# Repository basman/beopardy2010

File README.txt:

Jeopardy game setup with software, hardware and firmware
based on the CCC beopardy project (2010).

Instead of the original CCC's microcontroller, this project uses an
Arduino Nano to control the buttons and lamps. The serial protocol
has been extended to indicate exactly at all times during the game
which players may buzz in and when.

The repo contains the following subdirectories:

arduino         - the firmware for the Arduino Nano, controlling the
                  button lamps and signalling the buttons over the 
                  serial port to the PC/laptop running beopardy_2010

beopardy_2010   - the Jeopardy game software, written in Perl+Tk
                  This program displays the game board and implements
                  the game.

hardware        - the game controller for push buttons and their lamps

References:

The code this fork is based on:
http://blogmal.42.org/misc/beopardy-2010.story

The legacy code with the different versions used at the CCC throughout the
years:
https://github.com/Sec42/beopardy-legacy

The new web based beopardy by Sec:
https://github.com/Sec42/beopardy

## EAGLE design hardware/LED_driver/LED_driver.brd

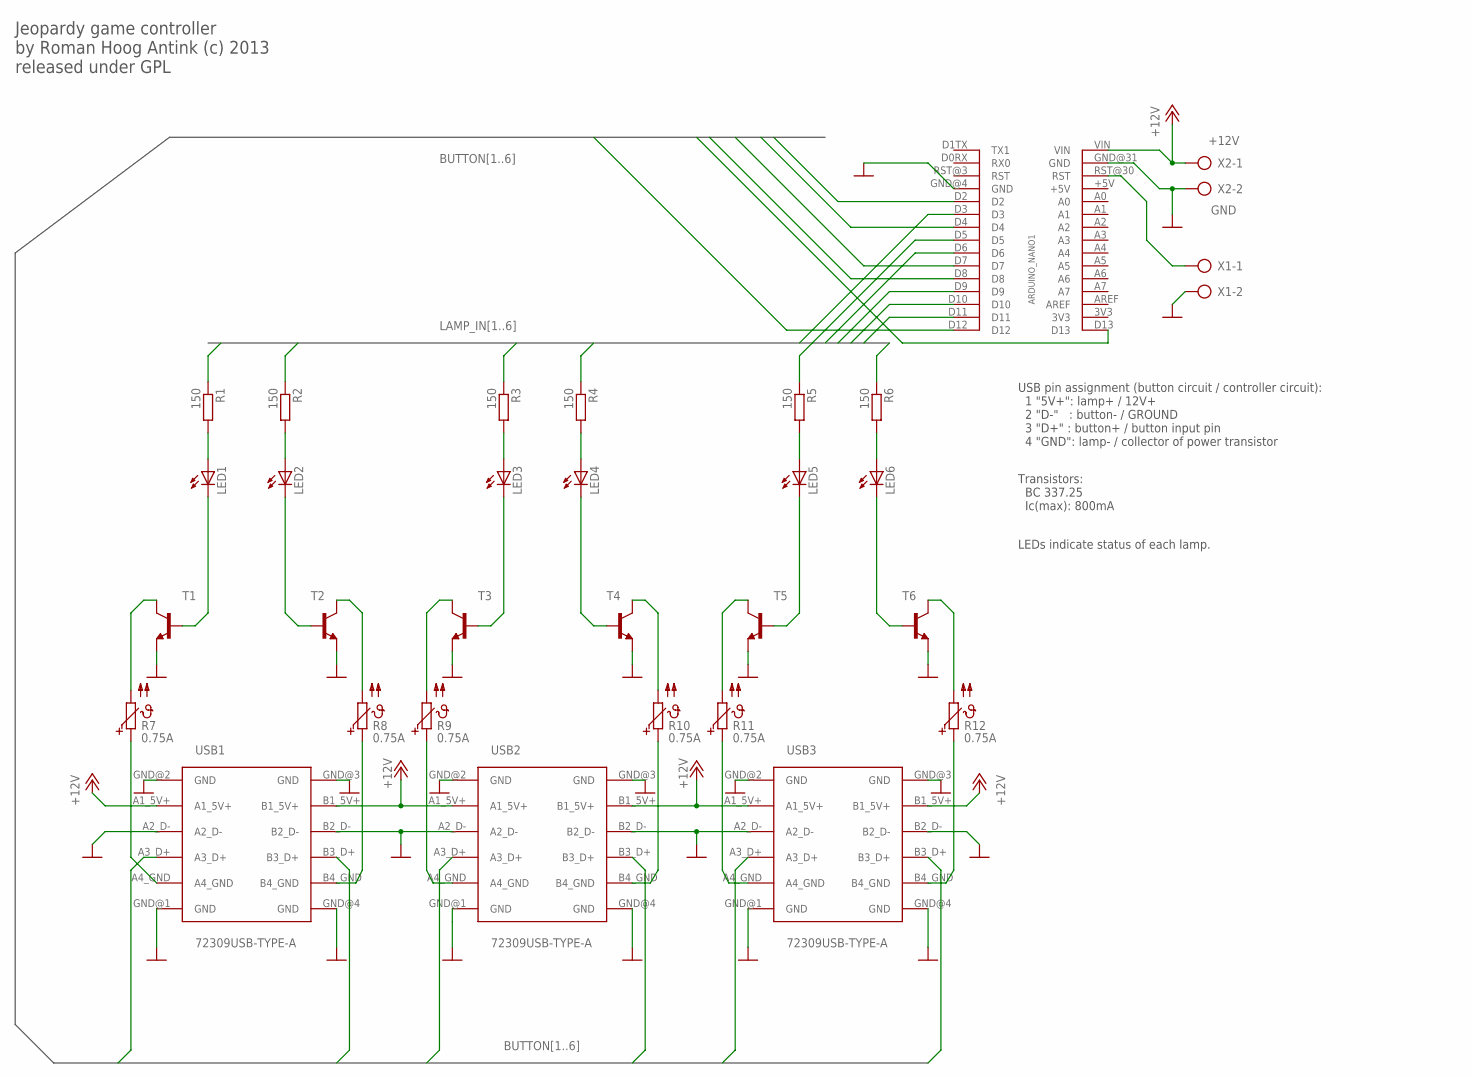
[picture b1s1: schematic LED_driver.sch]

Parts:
ARDUINO_NANO1: ARDUINO-NANO-SHIELD-CON
LED1, LED2, LED3, LED4, LED5, LED6: LED3MM
R1, R2, R3, R4, R5, R6: 150; 0207/10
R7, R8, R9, R10, R11, R12: 0.75A; PTC
T1, T2, T3, T4, T5, T6: -NPN-TO92; TO92
USB1, USB2, USB3: 72309USB-TYPE-A; 72309
X1, X2: AK300/2

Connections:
+12V: ARDUINO_NANO1.VIN, USB1.A1_5V+, USB1.B1_5V+, USB2.A1_5V+, USB2.B1_5V+, USB3.A1_5V+, USB3.B1_5V+, X2.1
BUTTON1: ARDUINO_NANO1.D2, USB1.A3_D+
BUTTON2: ARDUINO_NANO1.D4, USB1.B3_D+
BUTTON3: ARDUINO_NANO1.D7, USB2.A3_D+
BUTTON4: ARDUINO_NANO1.D8, USB2.B3_D+
BUTTON5: ARDUINO_NANO1.D12, USB3.A3_D+
BUTTON6: ARDUINO_NANO1.D13, USB3.B3_D+
GND: ARDUINO_NANO1.GND@4 (GND), ARDUINO_NANO1.GND@31 (GND), T1.1 (E), T2.1 (E), T3.1 (E), T4.1 (E), T5.1 (E), T6.1 (E), USB1.A2_D-, USB1.B2_D-, USB1.GND@1 (GND), USB1.GND@2 (GND), USB1.GND@3 (GND), USB1.GND@4 (GND), USB2.A2_D-, USB2.B2_D-, USB2.GND@1 (GND), USB2.GND@2 (GND), USB2.GND@3 (GND), USB2.GND@4 (GND), USB3.A2_D-, USB3.B2_D-, USB3.GND@1 (GND), USB3.GND@2 (GND), USB3.GND@3 (GND), USB3.GND@4 (GND), X1.2, X2.2
LAMP_IN1: ARDUINO_NANO1.D3, R1.1
LAMP_IN2: ARDUINO_NANO1.D5, R2.1
LAMP_IN3: ARDUINO_NANO1.D6, R3.1
LAMP_IN4: ARDUINO_NANO1.D9, R4.1
LAMP_IN5: ARDUINO_NANO1.D10, R5.1
LAMP_IN6: ARDUINO_NANO1.D11, R6.1
unnamed: LED6.A, R6.2
unnamed: R7.2, T1.3 (C)
unnamed: R8.1, USB1.B4_GND
unnamed: R9.1, USB2.A4_GND
unnamed: R10.2, T4.3 (C)
unnamed: R11.1, USB3.A4_GND
unnamed: LED1.K (C), T1.2 (B)
unnamed: LED2.K (C), T2.2 (B)
unnamed: LED3.K (C), T3.2 (B)
unnamed: LED4.K (C), T4.2 (B)
unnamed: LED5.K (C), T5.2 (B)
unnamed: LED6.K (C), T6.2 (B)
unnamed: R12.2, T6.3 (C)
unnamed: LED5.A, R5.2
unnamed: LED4.A, R4.2
unnamed: LED3.A, R3.2
unnamed: LED2.A, R2.2
unnamed: LED1.A, R1.2
unnamed: ARDUINO_NANO1.RST@30 (RST), X1.1
unnamed: R7.1, USB1.A4_GND
unnamed: R8.2, T2.3 (C)
unnamed: R9.2, T3.3 (C)
unnamed: R10.1, USB2.B4_GND
unnamed: R11.2, T5.3 (C)
unnamed: R12.1, USB3.B4_GND

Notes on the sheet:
USB pin assignment (button circuit / controller circuit): 1 "5V+": lamp+ / 12V+ 2 "D-" : button- / GROUND 3 "D+" : button+ / button input pin 4 "GND": lamp- / collector of power transistor
Jeopardy game controller by Roman Hoog Antink (c) 2013 released under GPL
Transistors: BC 337.25 Ic(max): 800mA
LEDs indicate status of each lamp.

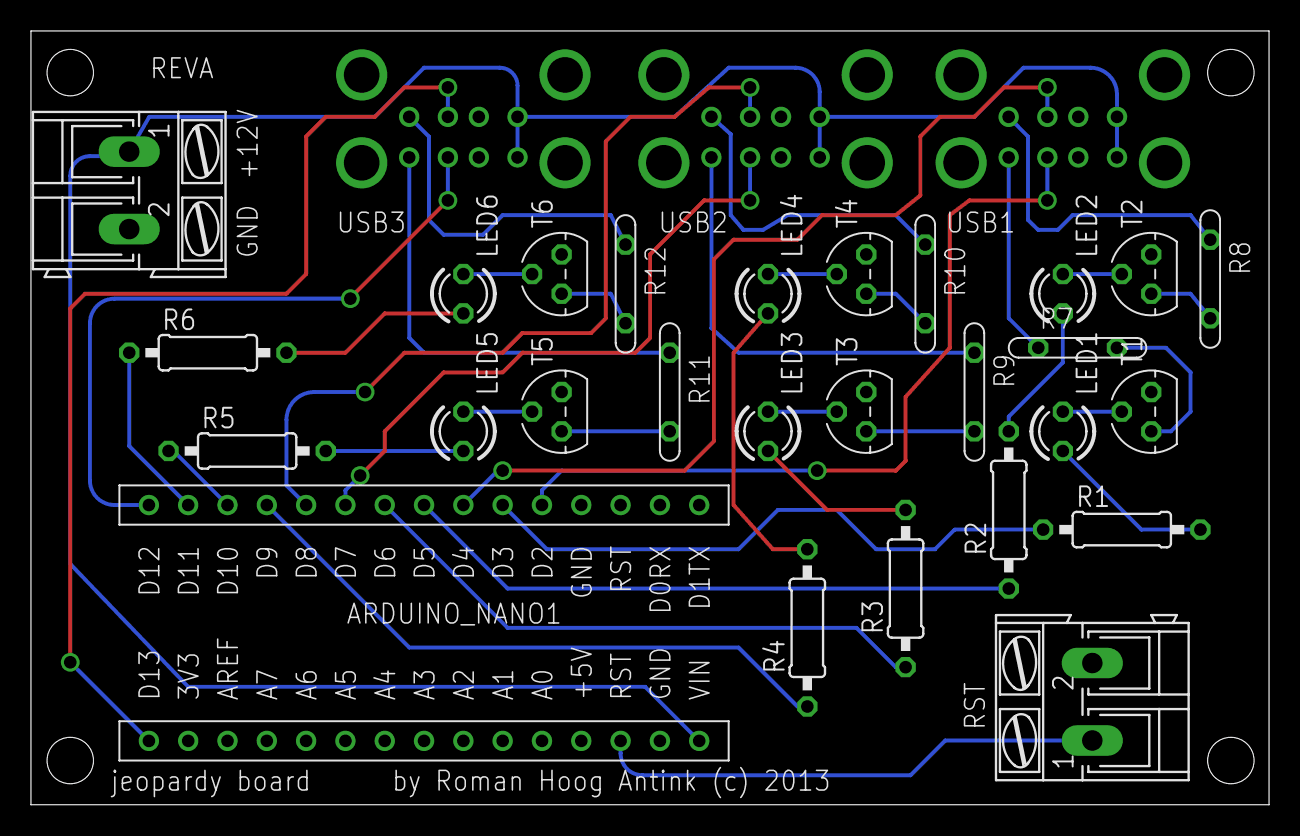
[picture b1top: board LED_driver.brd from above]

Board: 2 copper layers, 80.0 x 50.0 mm, 30 parts (0 on the bottom side), 39 nets.

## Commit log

2013-03-29 initial import (implementation of original CCC protocol)
2013-04-02 adjust all pins. add minimum lamp control.
2013-04-03 new feature: suppress buttons
2013-04-12 animate lamps and fix button suppression
2013-04-14 ignore carriage return
2013-04-14 code cleanup: remove trailing spaces
2013-04-14 import CCC beopardy 2010
2013-04-14 set serial /dev/ttyUSB0, speed 9600
2013-04-14 soundd: disable mood
2013-04-14 beopardy: add file access error messages
2013-04-14 beopardy: edit font selectors for Ubuntu 12.04
2013-04-14 add dummy input files, so beopardy can start
2013-04-20 configure for 6 players
2013-04-22 implement O command: oops, ignore last button
2013-04-22 add serial protocol documentation
2013-04-22 add error response to serial documentation
2013-04-23 cleanup TODO
2013-04-23 fix comment
2013-04-23 reset lamps after F (false) and O (oops) commands
2013-05-04 lamp animation: quick first flash
2013-05-09 begin implementation of serial protocol extension
2013-05-09 implement command 'N', switching off all buttons and lamps
2013-05-09 improve error message (connect sound server)
2013-05-09 more of serial protocol extension
2013-05-09 use serial command 'N' to silence all buttons and lamps after 'Start' has been clicked
2013-05-09 don't reset board if empty string received from board
2013-07-21 disable "Hey, ray!" popup
2013-07-21 fix unitialized warning
2013-07-22 try multiple ttyUSBx ports
2013-07-22 show popup when serial connection is lost
2013-07-22 create TODO
2013-07-22 open serial port without creating file and no clobber
2013-07-22 ser_reset may be used as callback or called directly
2013-07-22 suppress warning about non numerical serial input
2013-07-22 improve serial input message
2013-07-22 fix ser_reset argument semantics
2013-07-22 fix failing ser_reset during startup
2013-07-22 add .gitignore
2013-07-22 again fix failing ser_reset at startup
2013-07-23 rephrase serial protocol documentation
2013-07-23 add hardware design (eagle and gerber files)
2013-07-23 add README.txt
2013-07-23 extend README.txt
2013-07-23 TODO: ser_reset during startup not solved
2013-07-23 add RTFM.ubuntu
2013-07-23 mark TODO
2013-07-23 move arduino files into subdirectory
    The arduino IDE complains otherwize when opening the source code
    beopardy.ino
2013-07-23 replace lamp animation algorithm
    The old algorithm was static. The new algo is based on parametrisation.
2013-07-26 comments and cosmetics
2013-07-26 reset buttons upon question begin
2013-07-26 wait for arduino to initialize
2013-07-26 Revert "fix failing ser_reset during startup"
    ser_reset is no longer used as first communication to game controller,
    so the retry thing has been removed.
2013-07-26 fix ser_startup()
2013-07-26 improve handling of serial disruption
2013-07-26 default to 4 players
2013-07-26 TODO: button activation delay and penalty
2013-07-26 reduce hardware startup delay
2013-08-24 update TODO
2013-09-03 soundd: add .aac file type
2013-09-03 beopardy: avoid reset 'F' if no button pressed
2013-09-03 beopardy: support JPG and PNG images
2013-09-03 beopardy: use UTF-8 encoding for input files
2013-09-03 beopardy: introduce new font size for categories
2013-09-03 beopardy: update error message and comments
2013-09-03 beopardy: no button reset on double jeopardy
2013-09-03 beopardy: use pixmap image in Jeopardy
2013-09-03 arduino: new command 1,2,3,...
2013-09-03 beopardy: convert source code to UTF-8
2013-09-03 beopardy: fix double jeopardy serial communication
2013-09-03 soundd: use mplayer for mp3
2013-09-03 beopardy: leave button locked after correct answer
2013-09-03 beopardy: fix indentation
2013-10-05 autostart of soundd
2013-10-05 begin implementation of hwproxy
2013-10-09 hwproxy: continue implementation
2013-10-09 arduino: fix R,N,1,F suppressing all buttons (double jeopardy)
2013-10-09 new question directory structure (reorganise sample files)
2013-10-09 implement new question directory structure
2013-10-09 fix regression of double jeopardy by new question directory structure
2013-10-09 update docu (new question directory structure)
2013-10-10 hwproxy: add MAC usbserial file pattern
2013-10-10 hwproxy: comment explaining mapping and grouping
2013-10-10 hwproxy: implement data relay
2013-10-10 hwproxy: implement hardware state recovery
2013-10-10 hwproxy: IO tweaking
2013-10-10 add 6th player's color
2013-10-10 update Test.jg to load without error (new question directory structure)
2013-10-10 hwproxy: fix hardware state recovery
2013-10-10 beopardy: no splash screen with readfile (-r)
2013-10-10 hwproxy: fix autostart of soundd and hwproxy
2013-10-11 hwproxy: cleanup message
2013-10-11 hwproxy: implement hardware emulator (-e)
2013-10-11 beopardy: improve hardware disconnect robustness
2013-10-11 beopardy: do not watch buttons during double jeopardy before first result
2013-10-11 beopardy: improve hardware disconnected messages
2013-10-11 hwproxy: improve emulator messages
2013-10-11 beopardy: continue on hardware disconnect robustness
2013-10-11 beopardy: also show a questions value next to the category
2013-10-11 beopardy: also show a questions value next to the category (cherry picked from commit da0a49aa954cf41afdd54aeb82d25e6f244fe601)
2013-10-12 arduino: fix R,N,1,F suppressing all buttons (double jeopardy) (cherry picked from commit 431b5bfb97c1b12a857f0b07c396d9a760e29b3b)
2013-10-12 update TODO
    fixed by 431b5bfb97c1b12a857f0b07c396d9a760e29b3b
2013-10-14 beopardy: inhibit ser_reset() without tty
2013-10-14 beopardy: fix image cache usage (prepare for animated GIF support)
2013-10-14 beopardy: GIF animation support
2013-10-15 doc: how to extract audio from youtube
2013-10-27 beopardy: play sound with start and duration parameters
2013-10-27 soundd: implement command line options --debug, --single, --help
2013-10-27 beopardy: allow fractions of seconds in sound time spec
2013-10-27 beopardy: GIF animations must specify frame duration
2013-10-28 beopardy: exchange colors of players 5 and 6
2013-11-01 beopardy: drop old README
2013-11-01 beopardy: mark possibly dead code
2013-11-01 soundd: support time spec in name expansion
2013-11-01 TODO: close question if no player left
2013-11-02 beopardy: fix ignored time spec on sound restart ('R')
2013-11-03 soundd: show full playback output if debug option set
2013-11-03 beopardy: fix double jeopardy sound
2013-11-03 TODO: abort sound question is a bad idea
    some sound questions are only 10 seconds in length. players
    wont buzz in so soon, as they are waiting for more context.
2013-11-04 beopardy: close question after all players failed answering
2013-11-05 beopardy: use as many questions per category as possible
2013-11-06 beopardy: random player with key 'r' (and 'R')
2013-11-18 beopardy: remove dead code
2013-11-18 beopardy: play intro music on Ctrl-m
2013-11-25 arduino: fading support for flash sequences
2013-11-26 arduino: complex flash sequence, different for odd and even buttons
2013-12-10 add double jeopardy to dummy question files
2013-12-10 beopardy: disable questions while splash window appears
2013-12-10 beopardy: prevent destroy on undef after double jeopardy and Oops
2013-12-10 beopardy: disable questions during double jeopardy dialog
2013-12-10 beopardy: allow re-entering double jeopardy
2014-01-19 add screenshots sound_q and edit_points
2014-01-19 add screenshots for development of new GUI
2014-01-19 add requirements for new GUI

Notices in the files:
hardware/LED_driver/LED_driver.brd:
jeopardy board by Roman Hoog Antink (c) 2013
